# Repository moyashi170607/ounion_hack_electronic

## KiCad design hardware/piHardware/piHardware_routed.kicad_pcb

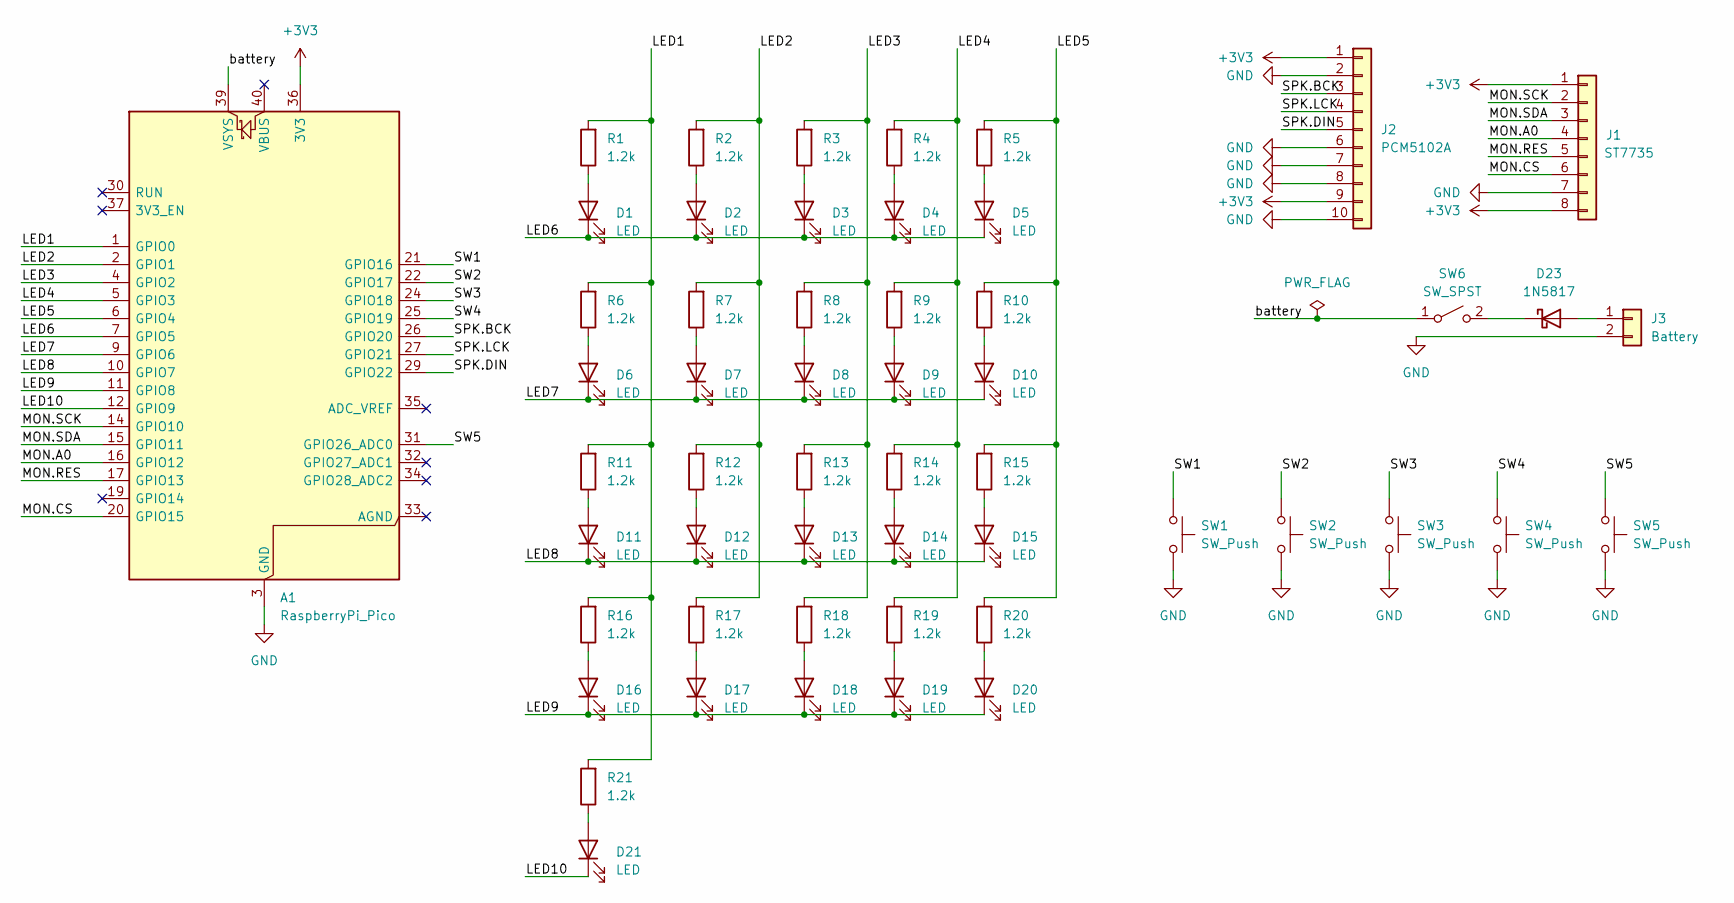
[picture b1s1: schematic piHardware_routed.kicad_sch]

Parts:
A1: RaspberryPi_Pico; RaspberryPi_Pico_Common_Unspecified
D1, D2, D3, D4, D5, D6, D7, D8, D9, D10, D11, D12, D13, D14, D15, D16, D17, D18, D19, D20, D21: LED; JST_XH_B2B-XH-A_1x02_P2.50mm_Vertical
D23: 1N5817; D_DO-41_SOD81_P10.16mm_Horizontal
J1: ST7735; PinHeader_1x08_P2.54mm_Vertical
J2: PCM5102A; PinHeader_1x10_P2.54mm_Vertical
J3: Battery; PinHeader_1x02_P2.54mm_Vertical
R1, R2, R3, R4, R5, R6, R7, R8, R9, R10, R11, R12, R13, R14, R15, R16, R17, R18, R19, R20, R21: 1.2k; R_Axial_DIN0207_L6.3mm_D2.5mm_P7.62mm_Horizontal
SW1, SW2, SW3, SW4, SW5: SW_Push; JST_XH_B2B-XH-A_1x02_P2.50mm_Vertical
SW6: SW_SPST; JST_XH_B2B-XH-A_1x02_P2.50mm_Vertical

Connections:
+3V3: A1.36 (3V3), J1.1, J1.8, J2.1, J2.9
/LED1: A1.1 (GPIO0), R1.2, R6.2, R11.2, R16.2, R21.2
/LED2: A1.2 (GPIO1), R2.2, R7.2, R12.2, R17.2
/LED3: A1.4 (GPIO2), R3.2, R8.2, R13.2, R18.2
/LED4: A1.5 (GPIO3), R4.2, R9.2, R14.2, R19.2
/LED5: A1.6 (GPIO4), R5.2, R10.2, R15.2, R20.2
/LED6: A1.7 (GPIO5), D1.1 (K), D2.1 (K), D3.1 (K), D4.1 (K), D5.1 (K)
/LED7: A1.9 (GPIO6), D6.1 (K), D7.1 (K), D8.1 (K), D9.1 (K), D10.1 (K)
/LED8: A1.10 (GPIO7), D11.1 (K), D12.1 (K), D13.1 (K), D14.1 (K), D15.1 (K)
/LED9: A1.11 (GPIO8), D16.1 (K), D17.1 (K), D18.1 (K), D19.1 (K), D20.1 (K)
/LED10: A1.12 (GPIO9), D21.1 (K)
/MON.A0: A1.16 (GPIO12), J1.4
/MON.CS: A1.20 (GPIO15), J1.6
/MON.RES: A1.17 (GPIO13), J1.5
/MON.SCK: A1.14 (GPIO10), J1.2
/MON.SDA: A1.15 (GPIO11), J1.3
/SPK.BCK: A1.26 (GPIO20), J2.3
/SPK.DIN: A1.29 (GPIO22), J2.5
/SPK.LCK: A1.27 (GPIO21), J2.4
/SW1: A1.21 (GPIO16), SW1.1
/SW2: A1.22 (GPIO17), SW2.1
/SW3: A1.24 (GPIO18), SW3.1
/SW4: A1.25 (GPIO19), SW4.1
/SW5: A1.31 (GPIO26_ADC0), SW5.1
/battery: A1.39 (VSYS), SW6.1 (A)
GND: A1.3 (GND), A1.8 (GND), A1.13 (GND), A1.18 (GND), A1.23 (GND), A1.28 (GND), A1.38 (GND), J1.7, J2.2, J2.6, J2.7, J2.8, J2.10, J3.2, SW1.2, SW2.2, SW3.2, SW4.2, SW5.2
unnamed: D1.2 (A), R1.1
unnamed: D2.2 (A), R2.1
unnamed: D3.2 (A), R3.1
unnamed: D4.2 (A), R4.1
unnamed: D5.2 (A), R5.1
unnamed: D6.2 (A), R6.1
unnamed: D7.2 (A), R7.1
unnamed: D8.2 (A), R8.1
unnamed: D9.2 (A), R9.1
unnamed: D10.2 (A), R10.1
unnamed: D11.2 (A), R11.1
unnamed: D12.2 (A), R12.1
unnamed: D13.2 (A), R13.1
unnamed: D14.2 (A), R14.1
unnamed: D15.2 (A), R15.1
unnamed: D16.2 (A), R16.1
unnamed: D17.2 (A), R17.1
unnamed: D18.2 (A), R18.1
unnamed: D19.2 (A), R19.1
unnamed: D20.2 (A), R20.1
unnamed: D21.2 (A), R21.1
unnamed: D23.2 (A), J3.1
unnamed: D23.1 (K), SW6.2 (B)

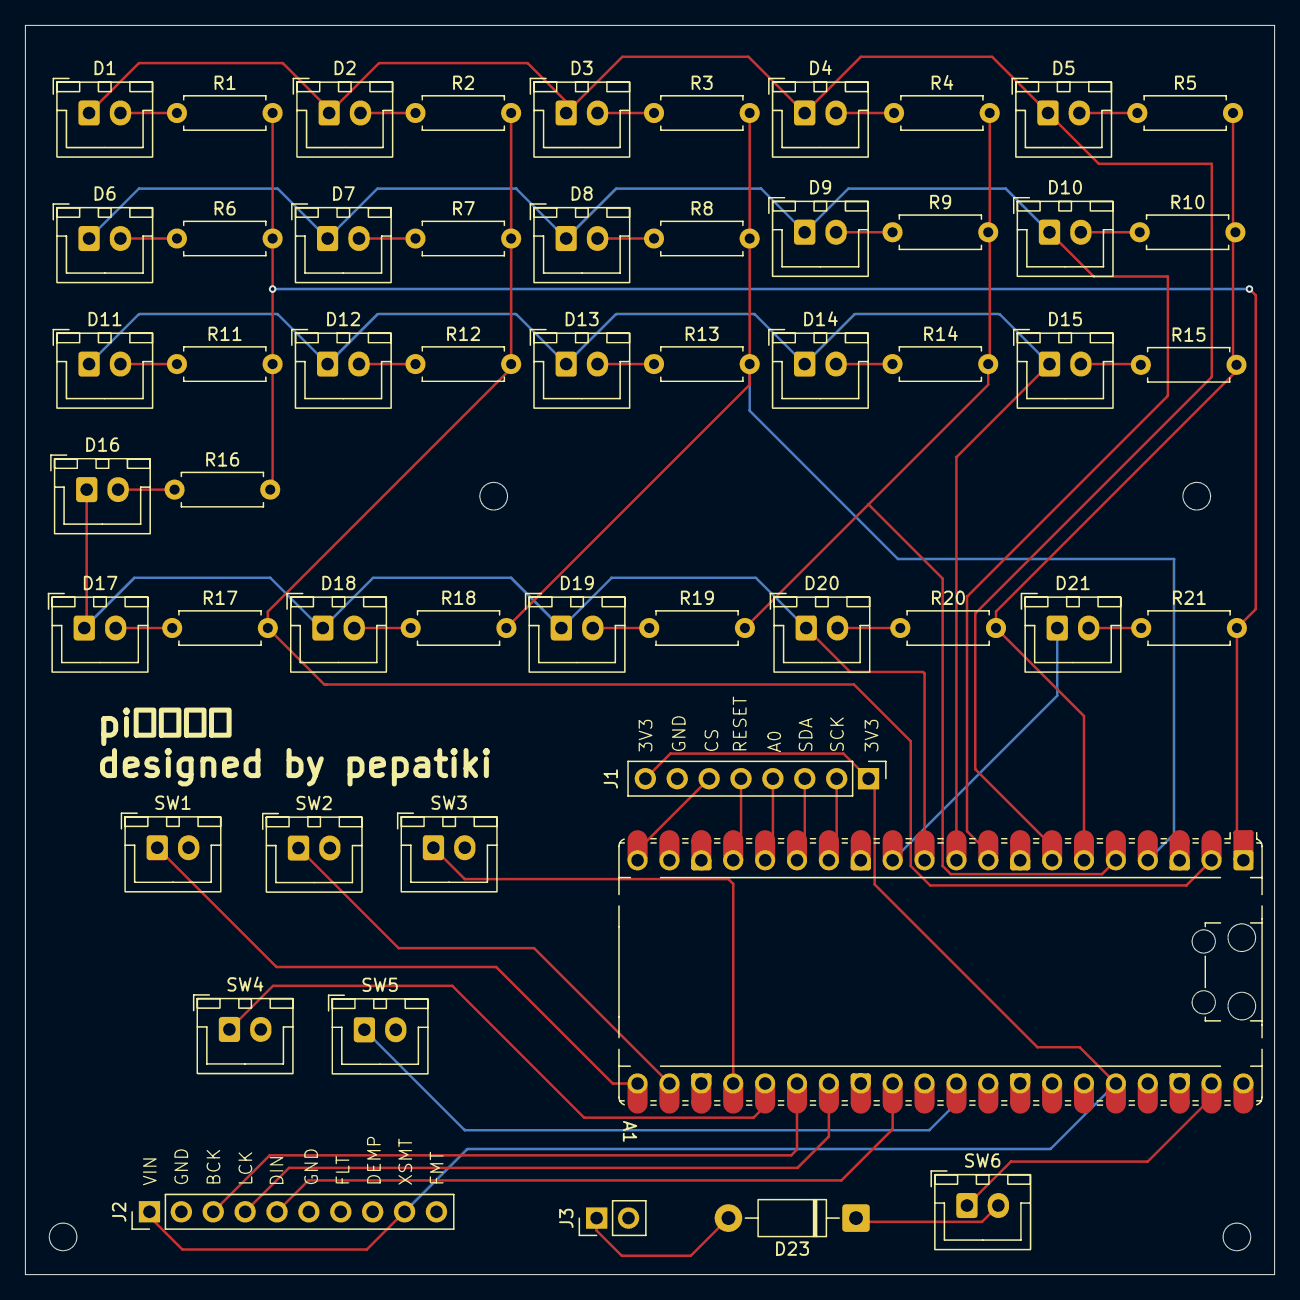
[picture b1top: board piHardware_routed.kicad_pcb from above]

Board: 2 copper layers, 99.5 x 99.5 mm, 53 parts (0 on the bottom side), 49 nets.
